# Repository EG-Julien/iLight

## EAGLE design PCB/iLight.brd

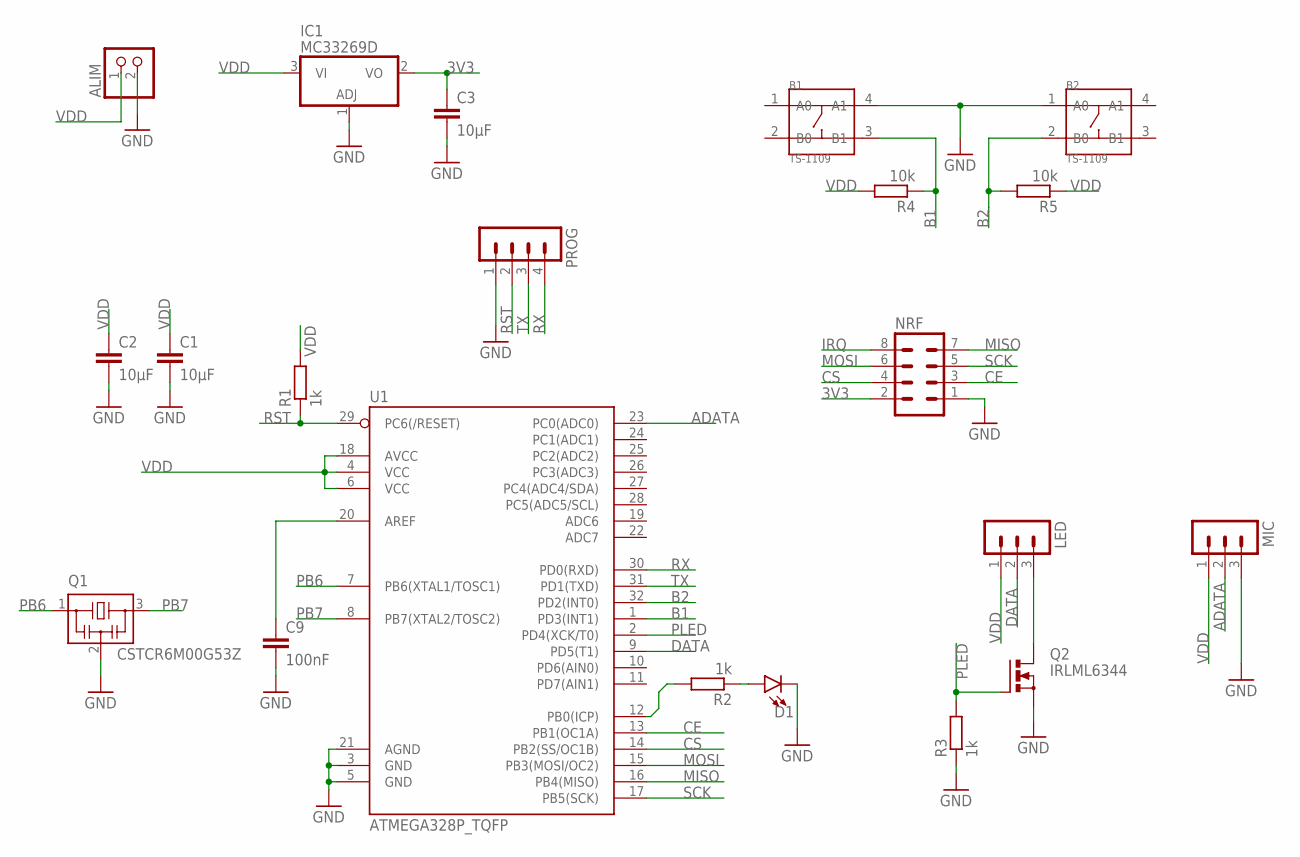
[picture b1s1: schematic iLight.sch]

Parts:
ALIM: PINHD-1X2; 1X02
B1, B2: TS-1109; SW4-6.0X6.0X5.0MM
C1, C2, C3: 10µF; C1206
C9: 100nF; C1206
D1: LED-FKIT-1206; FKIT-LED-1206
IC1: MC33269D; DPACK
LED: MA03-1
MIC: MA03-1
NRF: MA04-2
PROG: MA04-1
Q1: CSTCR6M00G53Z; CSTCR6M
Q2: IRLML6344; SOT-23
R1, R2, R3: 1k; R1206
R4, R5: 10k; R1206
U1: ATMEGA328P_TQFP; TQFP32-08

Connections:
3V3: C3.1, IC1.2 (VO), NRF.2
ADATA: MIC.2, U1.23 (PC0(ADC0))
B1: B1.3 (B1), R4.1, U1.1 (PD3(INT1))
B2: B2.2 (B0), R5.2, U1.32 (PD2(INT0))
CE: NRF.3, U1.13 (PB1(OC1A))
CS: NRF.4, U1.14 (PB2(SS/OC1B))
DATA: LED.2, U1.9 (PD5(T1))
GND: ALIM.2, B1.4 (A1), B2.1 (A0), C1.2, C2.2, C3.2, C9.2, D1.C, IC1.1 (ADJ), MIC.3, NRF.1, PROG.1, Q1.2, Q2.P2 (S), R3.1, U1.3 (GND), U1.5 (GND), U1.21 (AGND)
IRQ: NRF.8
MISO: NRF.7, U1.16 (PB4(MISO))
MOSI: NRF.6, U1.15 (PB3(MOSI/OC2))
unnamed: C9.1, U1.20 (AREF)
unnamed: LED.3, Q2.P3 (D)
unnamed: R2.2, U1.12 (PB0(ICP))
unnamed: D1.A, R2.1
PB6: Q1.1, U1.7 (PB6(XTAL1/TOSC1))
PB7: Q1.3, U1.8 (PB7(XTAL2/TOSC2))
PLED: Q2.P1 (G), R3.2, U1.2 (PD4(XCK/T0))
RST: PROG.2, R1.1, U1.29 (PC6(/RESET))
RX: PROG.4, U1.30 (PD0(RXD))
SCK: NRF.5, U1.17 (PB5(SCK))
TX: PROG.3, U1.31 (PD1(TXD))
VDD: ALIM.1, C1.1, C2.1, IC1.3 (VI), LED.1, MIC.1, R1.2, R4.2, R5.1, U1.4 (VCC), U1.6 (VCC), U1.18 (AVCC)

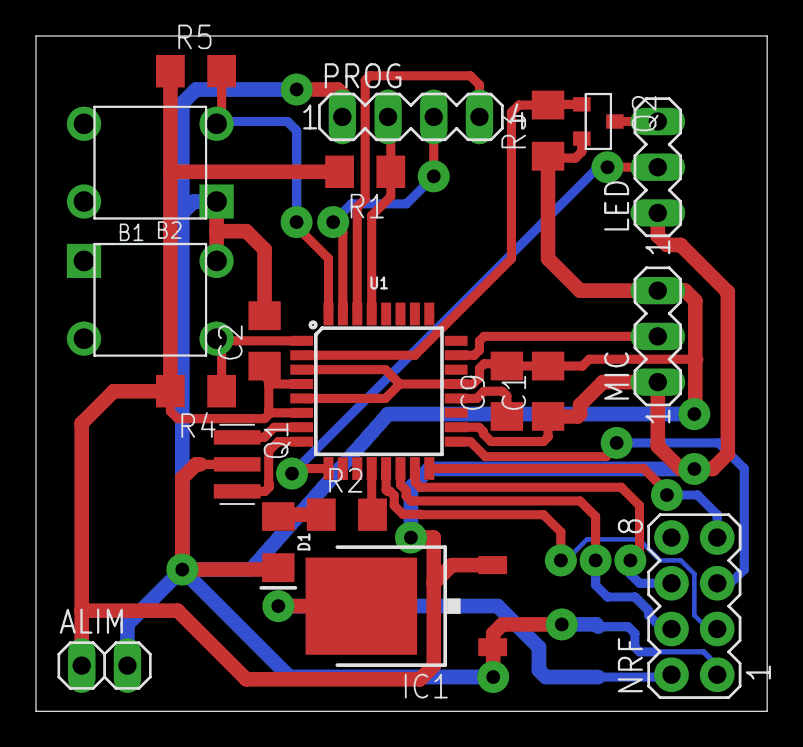
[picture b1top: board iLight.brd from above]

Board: 2 copper layers, 40.6 x 37.5 mm, 21 parts (1 on the bottom side), 22 nets.

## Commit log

2018-08-18 iLight | A simple board to control LED strip

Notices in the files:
parts and their libraries:
SparkFun-LED: Licensing: Creative Commons ShareAlike 4.0 International - https://creativecommons.org/licenses/by-sa/4.0
